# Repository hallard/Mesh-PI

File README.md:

# Mesh-PI — The tiniest LoRa board for Raspberry Pi

**Mesh-PI** is, as far as I know, the **smallest SX1262 LoRa board ever made for the Raspberry Pi**. It's built around the ultra-small **10×10 mm** [Ebyte **E22-900MM22S**][e22] (Semtech **SX1262**, 868/915 MHz) module — the board is barely bigger than the module itself.

It's designed to run [Meshtastic][meshtastic] with the Linux-native daemon [`meshtasticd`][meshtasticd], but since it's just a plain SX1262 on the SPI bus, it works with **any LoRa / LoRa-mesh stack** — Meshtastic, [Reticulum / RNode][reticulum], your own [RadioLib][radiolib] project… Ideal for a compact, always-on **router / MQTT gateway** node, with the full power of Linux behind it: SSH, MQTT, Home Assistant, scripting…

## Features

**Version 1.0**

- Placement for **Ebyte E22-900MM22S** module — SX1262, 868/915 MHz ISM, up to **22 dBm**, ~7 km range, 10×10 mm
- **u.FL** antenna connector — or solder an edge-mount **SMA** connector / wire antenna instead
- **2 status LEDs** (Green = OK, Red = fault) driven from GPIO
- Powered straight from the Pi **3.3 V** rail, with proper bulk + low-ESR decoupling (100 µF tantalum + 47 µF MLCC + 100 nF)
- Designed for **`meshtasticd`** (Meshtastic Linux-native)

## Design choices

Mesh-PI is deliberately **minimal and purpose-built for a static router node** — small, cheap, efficient, and it does exactly that job, perfectly.

- **No GPS — on purpose.** Dropped to save space and cost. A fixed router doesn't move, so its location is set once as a *fixed position* in Meshtastic; an on-board GPS would only add size, price and power draw for nothing.
- **22 dBm — on purpose.** The board uses the SX1262's native **22 dBm** rather than a 1 W (30 dBm) amplified front-end. Going 1 W would mean tapping the Pi **5 V** rail and adding a dedicated 3.3 V regulator for the extra current — which would blow up the whole "tiny shield" idea. At 22 dBm the module runs **straight off the Pi 3.3 V** and stays cool. The E22-900 covers **850–930 MHz**, so it works in **EU868**, **US915** and the other 900 MHz regions. ⚠️ Meshtastic does **not** auto-cap the output to the EU legal limit — you must set the TX power yourself (see the **Power limits & regulations** section below).

Small, focused, and it just works. 🎯

## Schematics

SPI is the classic MOSI / MISO / SCLK. **NSS (chip-select) sits on GPIO25** — a free GPIO, *not* CE0 — to avoid the `cs-gpios` conflict of recent Raspberry Pi kernels (meshtasticd / RadioLib drives it directly). The RF switch uses **DIO2 for TX** (`DIO2_AS_RF_SWITCH`) and a GPIO for RX.

```
Raspberry PI            E22-900MM22S (SX1262)
   GPIO25  <---->  NSS   (chip select)
   SCLK    <---->  SCK
   MOSI    <---->  MOSI
   MISO    <---->  MISO
   GPIO23  <---->  NRST  (reset, active low)
   GPIO27  <---->  BUSY
   GPIO24  <---->  DIO1  (IRQ)
   GPIO22  <---->  RXEN
   DIO2    <---->  TXEN  (tied together -> DIO2_AS_RF_SWITCH)
   DIO3    :  not connected  (32 MHz XTAL on module, no TCXO)

Raspberry PI         On Board LEDs
   GPIO18  <---->  Green LED (status OK)
   GPIO17  <---->  Red LED   (fault)
```

## Assembled boards

## Mounting

Mesh-PI is a **partial HAT** — its 2×7 socket plugs onto a **14-pin block of the Pi's 40-pin GPIO header: physical pins 11 → 24**. Position it *exactly* as shown, and it can only go one way:

- The socket covers **pins 11–24** — pins **1–10 stay free** on the SD-card side, **25–40 free** on the other side.
- Mount it **exactly as in the photo above** — don't shift it by a row or plug it in flipped: any offset puts the radio on the wrong pins.
- Press it **fully and squarely** onto the header *before* powering the Pi.

## 3D printed case

Need an enclosure? **Finn** designed a neat [Meshtastic Raspberry Pi Zero 2 W case with foot](https://www.printables.com/model/1252555-meshtastic-raspberry-pi-zero-2-w-case-with-foot) on Printables — a simple, stationary enclosure with an integrated stand, purpose-built for a headless Pi Zero 2 W LoRa node (no buttons, GPS or display to cut out). A great way to finish off a Mesh-PI router.

Big thanks to **Finn** for designing and sharing it! 🙏

## Software — meshtasticd

Install the Meshtastic Linux daemon (see the [official docs][meshtasticd]), then declare the radio in `/etc/meshtasticd/config.yaml`:

```yaml
Lora:
  Module: sx1262
  CS: 25
  IRQ: 24
  Busy: 27
  Reset: 23
  RXen: 22
  DIO2_AS_RF_SWITCH: true
  # No DIO3_TCXO_VOLTAGE — the E22-900MM22S uses a passive 32 MHz XTAL, not a TCXO
```

> ⚠️ **Do NOT** set `DIO3_TCXO_VOLTAGE` on this board. The **MM22S** variant is crystal-based; setting it would tell the SX1262 to power a non-existent TCXO and the radio would fail to init (`-707`). *(The larger M22S is TCXO — that's a different module.)*

Enable SPI and set the boot state of the reset / LED pins in `/boot/firmware/config.txt`:

```
dtparam=spi=on

# Keep the radio out of reset from the bootloader (NRST is active-low -> drive high)
gpio=23=op,dh
# LEDs off at boot (active-high -> drive low)
gpio=17,18=op,dl
```

Then set the LoRa region and node role from any Meshtastic client (the phone app), or the [Meshtastic Python CLI](https://meshtastic.org/docs/software/python/cli/installation/) — install it with `pipx install meshtastic`, then:

```
meshtastic --host localhost --set lora.region EU_868 --set device.role ROUTER
```

## ⚠️ Power limits & regulations

The E22-900MM22S can transmit at up to **22 dBm (~160 mW)**, and Meshtastic's `EU_868` preset will happily let it — on a Mesh-PI I measured `Final Tx power: 22 dBm`, **not** capped to any lower value.

**In the EU, the 868 MHz ISM band is legally limited** — over most of the band that's **25 mW ERP (~14 dBm)**. Running the radio at 22 dBm where that isn't permitted is a **regulatory violation**, and it is entirely up to you to comply with your own country's rules.

So on this board, **set the TX power yourself** — don't leave it at the region maximum. It's the `lora.tx_power` setting, in dBm:

```
meshtastic --host localhost --set lora.tx_power 14
```

(or in the phone app: **LoRa → Tx Power**). A value of `0` means *"use the region maximum"*, so set an explicit value — e.g. **14** for the EU — to stay within your legal limit.

> **Disclaimer:** you alone are responsible for operating this board within your local radio regulations. The author is **not responsible** for any misuse, non-compliant configuration, or interference caused by running it above the legal power limit for your region.

## Status LEDs

The two on-board LEDs give an at-a-glance health status, blinked from GPIO by a small `systemd` service:

- 🟢 **Green (GPIO18)** blinks when WiFi *and* `meshtasticd` are both up
- 🔴 **Red (GPIO17)** blinks when either one is down

The script is [`scripts/monitoring-led.sh`](scripts/monitoring-led.sh) (uses `gpioset` from libgpiod v2).

### Install

```bash
# 1. Copy the script in place
sudo install -m 0755 scripts/monitoring-led.sh /usr/local/bin/monitoring-led.sh

# 2. Create the systemd service
sudo tee /etc/systemd/system/monitoring-led.service > /dev/null <<'EOF'
[Unit]
Description=Mesh-PI monitoring LEDs (green=OK, red=fault)
After=NetworkManager.service meshtasticd.service

[Service]
Type=simple
ExecStart=/usr/local/bin/monitoring-led.sh
Restart=always
RestartSec=5

[Install]
WantedBy=multi-user.target
EOF

# 3. Enable + start (runs at every boot)
sudo systemctl enable --now monitoring-led
```

Check with `systemctl status monitoring-led` — the green LED should start blinking. The `gpio=17,18=op,dl` line in `config.txt` above keeps both LEDs off during boot, before the service takes over.

## License

This design is licensed under a [Creative Commons Attribution-NonCommercial-ShareAlike 4.0 International License][cc-by-nc-sa] — build it, tweak it, share it, but **not for commercial use**.

[![License: CC BY-NC-SA 4.0][cc-badge]][cc-by-nc-sa]

## Lazy building your own?

If I put a batch of these on [Lectronz][lectronz], you'll be able to order one there.

[][lectronz]

## Misc

News and other projects on my [blog][blog].

[meshtastic]: https://meshtastic.org
[meshtasticd]: https://meshtastic.org/docs/software/linux/installation/
[reticulum]: https://reticulum.network/
[radiolib]: https://github.com/jgromes/RadioLib
[e22]: https://www.cdebyte.com/products/E22-900MM22S
[lectronz]: https://lectronz.com/stores/hallard
[cc-by-nc-sa]: https://creativecommons.org/licenses/by-nc-sa/4.0/
[cc-badge]: https://licensebuttons.net/l/by-nc-sa/4.0/88x31.png
[blog]: https://hallard.me

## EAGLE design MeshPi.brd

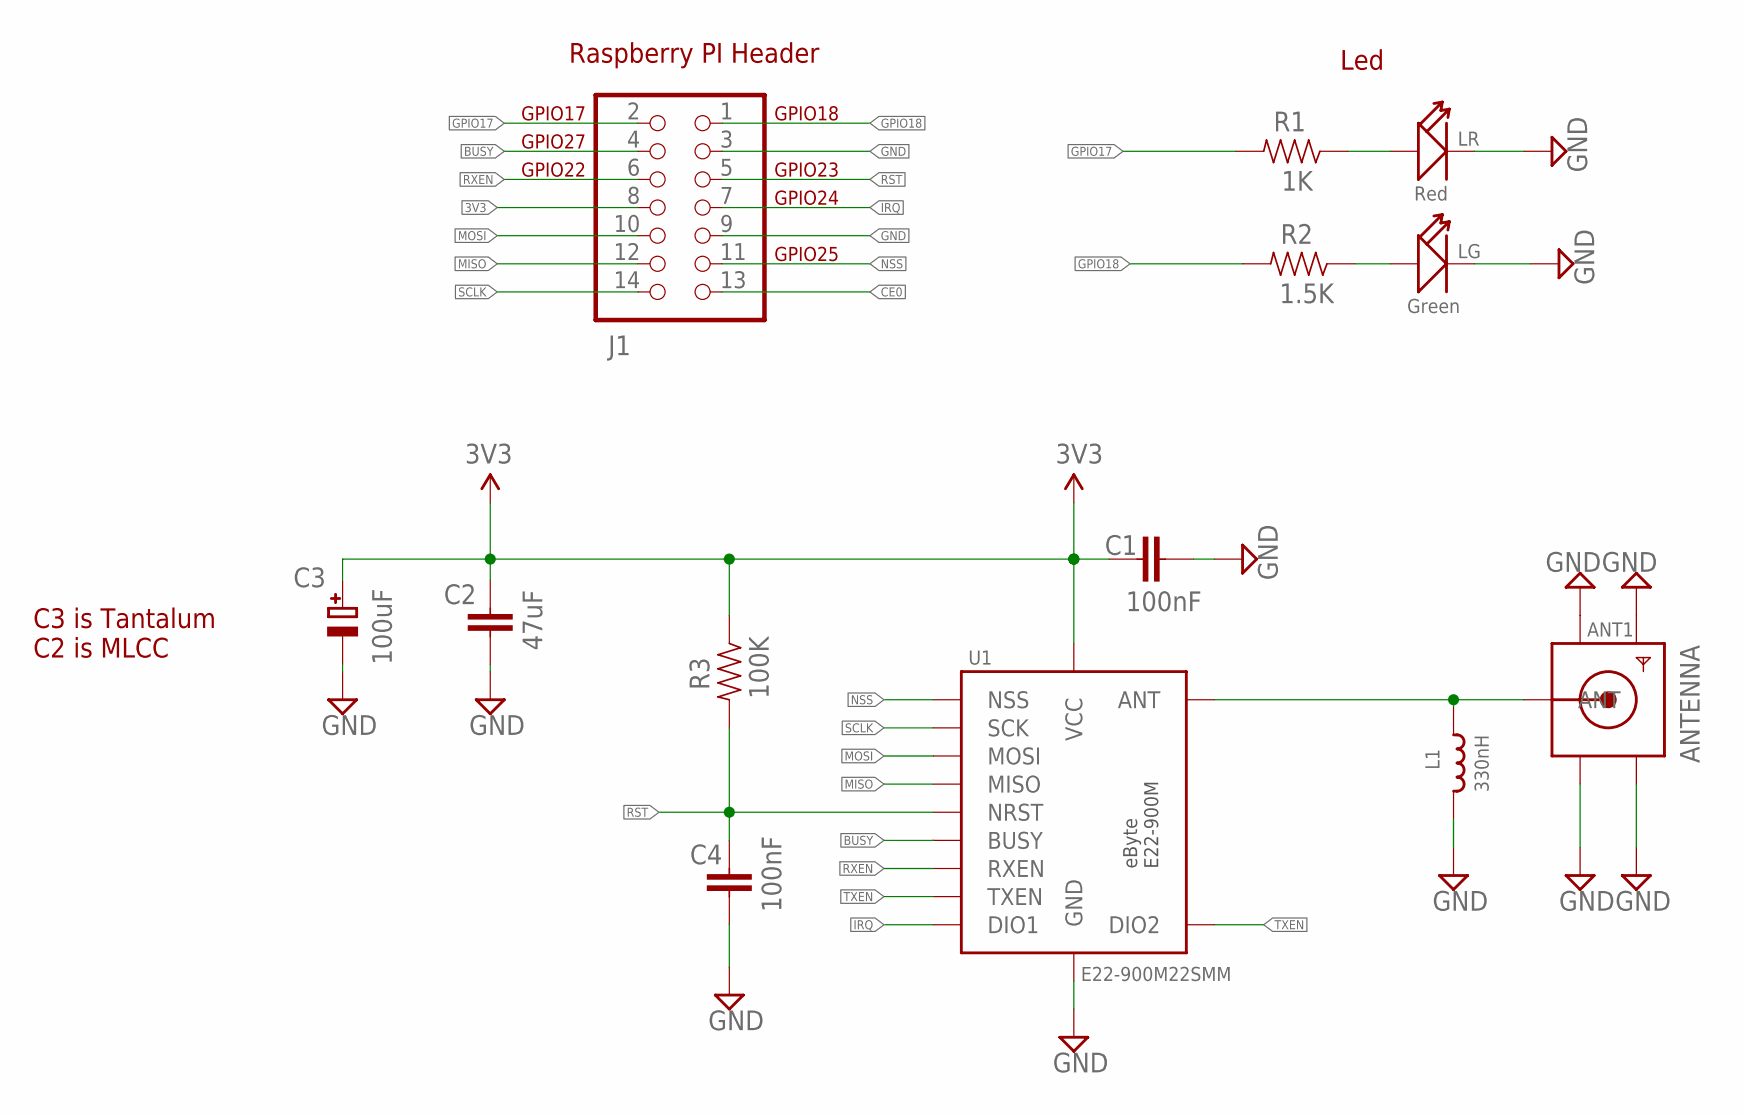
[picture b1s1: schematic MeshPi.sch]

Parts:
ANT1: SMACONNECTOR_EDGE_UFL; SMA_EDGELAUNCH_UFL
C1, C4: 100nF; 0402-CAP
C2: 47uF; 1206
C3: 100uF; EIA3528-21/B-R
J1: PINHD-2X7; 2X07
L1: 330nH; _0603MP
LG: Green; LED-0402
LR: Red; LED-0402
R1: 1K; 0402-RES
R2: 1.5K; 0402-RES
R3: 100K; 0402-RES
U1: E22-900M22SMM; E22-900MM2S

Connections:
3V3: C1.2, C2.2, C3.+, J1.8, R3.1, U1.P$1 (VCC)
ANTENNA: ANT1.P (ANT), L1.1, U1.P$6 (ANT)
BUSY: J1.4, U1.P$11 (BUSY)
CE0: J1.13
GND: ANT1.GND@1 (GND1), ANT1.GND@2 (GND2), ANT1.GND@3 (GND3), ANT1.GND@4 (GND4), C1.1, C2.1, C3.-, C4.1, J1.3, J1.9, L1.2, LG.-, LR.-, U1.P$2 (GND), U1.P$7 (GND), U1.P$16 (GND)
GPIO17: J1.2, R1.2
GPIO18: J1.1, R2.2
IRQ: J1.7, U1.P$20 (DIO1)
MISO: J1.12, U1.P$12 (MISO)
MOSI: J1.10, U1.P$13 (MOSI)
unnamed: LR.+, R1.1
unnamed: LG.+, R2.1
NSS: J1.11, U1.P$14 (NSS)
RST: C4.2, J1.5, R3.2, U1.P$3 (NRST)
RXEN: J1.6, U1.P$10 (RXEN)
SCLK: J1.14, U1.P$15 (SCK)
TXEN: U1.P$9 (TXEN), U1.P$19 (DIO2)

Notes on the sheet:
C3 is Tantalum C2 is MLCC
Raspberry PI Header
Led
GPIO18
GPIO23
GPIO24
GPIO25
GPIO17
GPIO27
GPIO22

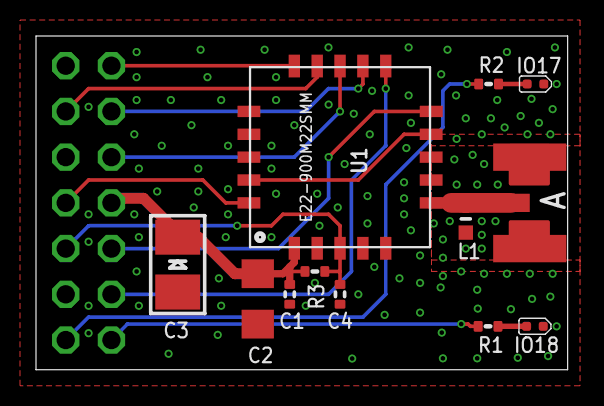
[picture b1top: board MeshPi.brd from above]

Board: 2 copper layers, 29.5 x 18.5 mm, 13 parts (1 on the bottom side), 16 nets.

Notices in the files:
parts and their libraries:
microbuilder: This work is placed in the public domain, and may be freely used for commercial and non-commercial work with the following conditions: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
SparkFun-Aesthetics: Licensing: Creative Commons ShareAlike 4.0 International - https://creativecommons.org/licenses/by-sa/4.0
